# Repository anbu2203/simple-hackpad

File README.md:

#  Simple Hackpad

A custom 4-key macro pad designed for productivity and built with the Seeed Studio XIAO RP2040. This project uses KMK Firmware (CircuitPython) to handle custom keymaps and RGB lighting effects.

### PCB Layout

This layout features optimized trace widths for power delivery to the LEDs.

### Schematic

The circuit design utilizes a direct-pin connection, avoiding the complexity of a diode matrix for a small 4-key setup.

### 3D CAD View - Style 1

### 3D CAD View - Style 2

### 3D CAD View - Full Assembly

This view was critical for ensuring the USB-C port on the XIAO would be easily accessible through a case cutout.

### 3D PCB VIEW:

This is a 3D render generated within KiCad to preview the final manufactured board.

### 3D full hackpad 
 
 It helped me visualize the spacing between the mechanical switches and the board edge.
 This is the master assembly model combining the PCB, switches, and the switch plate.

## Firmware & Features
The firmware is built using KMK. It includes:
- Custom Macros: Configured for KiCad shortcuts and media controls.
- RGB Screensaver:A rainbow animation that activates during idle time.
- CircuitPython: Easy to edit on the fly by just saving the `code.py` file.

## Repository Structure
- `firmware`: The `code.py` and configuration files for KMK.
- `hardware`: KiCad schematic and the `.step` 3D model.
- `README-IMAGES`: Visuals used in this documentation.

### Specifications BOM:

- 4x Cherry MX Switches
- 2x SK6812 MINI Leds
- 1x XIAO RP2040
- 4x Blank DSA Keycaps
- 4x M3x16 Bolt
- 4x M3 Heatset

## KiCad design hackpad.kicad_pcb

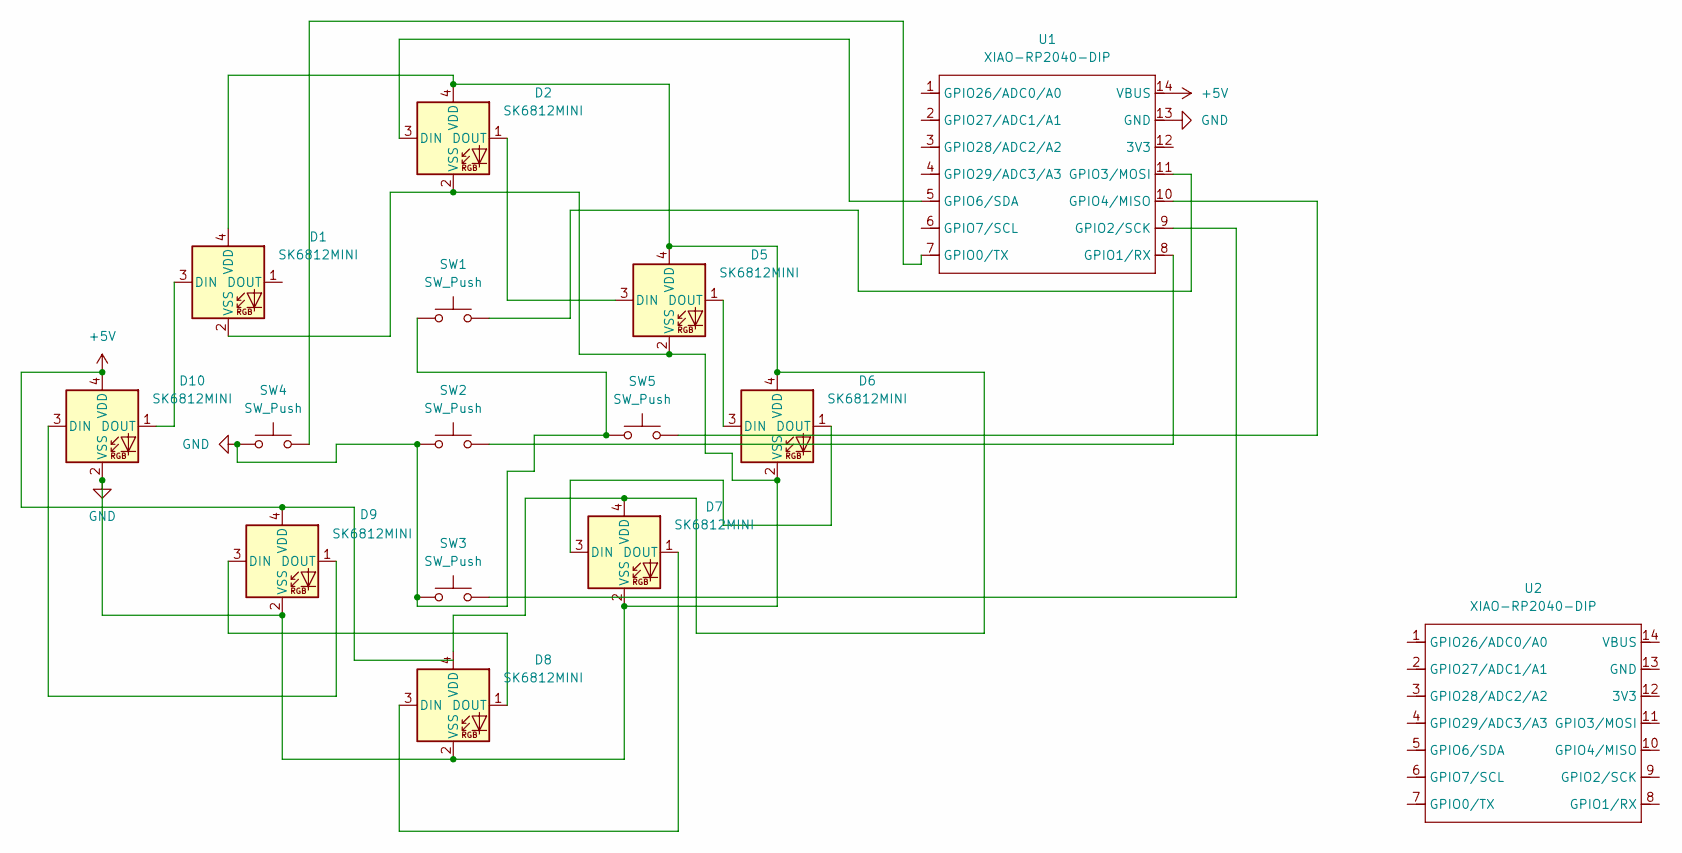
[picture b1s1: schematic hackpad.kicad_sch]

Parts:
D1, D2, D5, D6, D7, D8, D9, D10: SK6812MINI; LED_SK6812MINI_PLCC4_3.5x3.5mm_P1.75mm
SW1, SW2, SW3, SW4, SW5: SW_Push; SW_Cherry_MX_1.00u_PCB
U1, U2: XIAO-RP2040-DIP; MCU_Seeed_ESP32C3

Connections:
+5V: D9.4 (VDD), D10.4 (VDD), U1.14 (VBUS)
GND: D1.2 (VSS), D2.2 (VSS), D5.2 (VSS), D6.2 (VSS), D7.2 (VSS), D8.2 (VSS), D9.2 (VSS), D10.2 (VSS), SW1.1, SW2.1, SW3.1, SW4.1, SW5.1, U1.13 (GND)
unnamed: D1.3 (DIN), D10.1 (DOUT)
unnamed: D1.4 (VDD), D2.4 (VDD), D5.4 (VDD), D6.4 (VDD), D7.4 (VDD), D8.4 (VDD)
unnamed: D2.3 (DIN), U1.5 (GPIO6/SDA)
unnamed: D2.1 (DOUT), D5.3 (DIN)
unnamed: D5.1 (DOUT), D6.3 (DIN)
unnamed: D6.1 (DOUT), D7.3 (DIN)
unnamed: D7.1 (DOUT), D8.3 (DIN)
unnamed: D8.1 (DOUT), D9.3 (DIN)
unnamed: D9.1 (DOUT), D10.3 (DIN)
unnamed: SW4.2, U1.7 (GPIO0/TX)
unnamed: SW2.2, U1.8 (GPIO1/RX)
unnamed: SW3.2, U1.9 (GPIO2/SCK)
unnamed: SW1.2, U1.11 (GPIO3/MOSI)
unnamed: SW5.2, U1.10 (GPIO4/MISO)

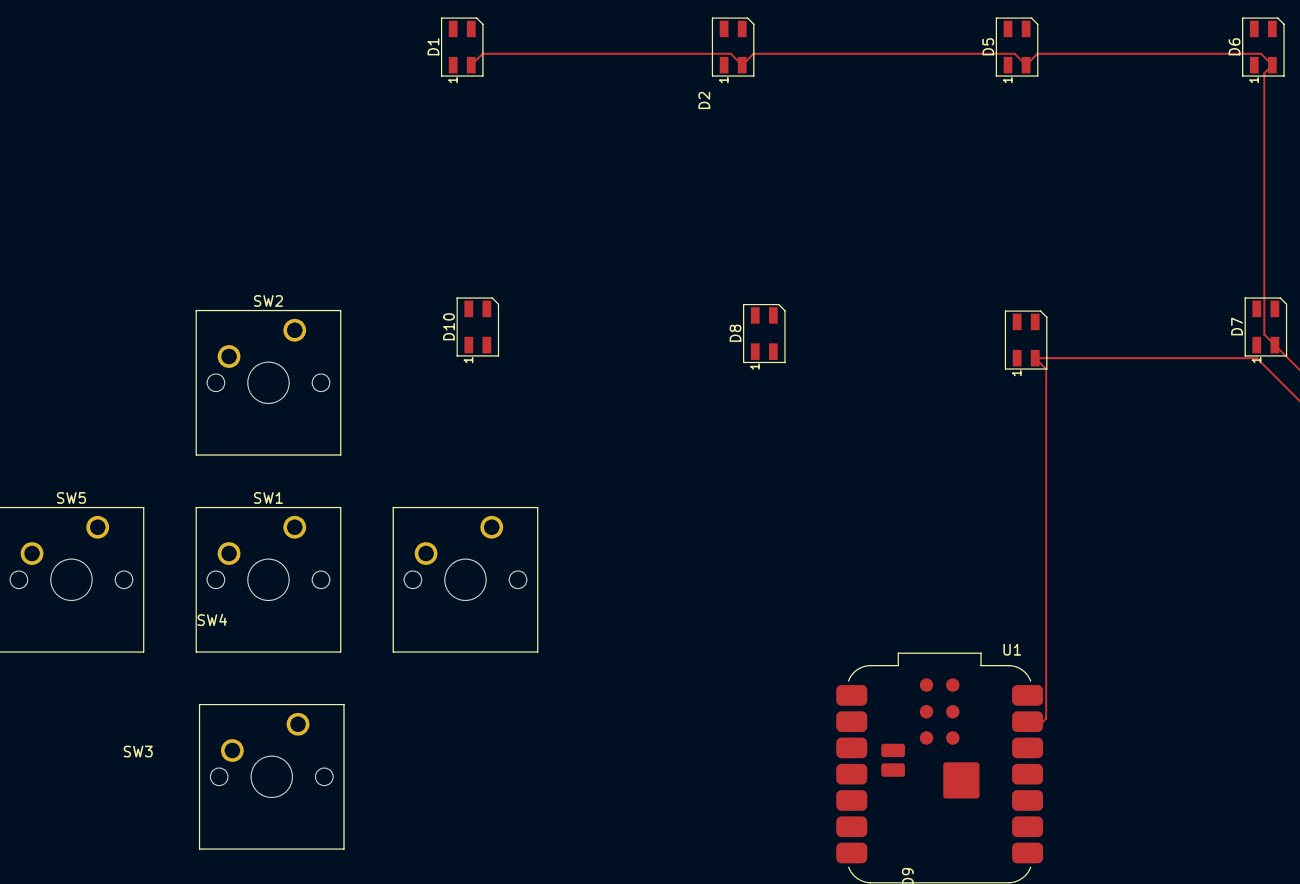
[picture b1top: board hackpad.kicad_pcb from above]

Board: 2 copper layers, 14 parts (0 on the bottom side), 16 nets.

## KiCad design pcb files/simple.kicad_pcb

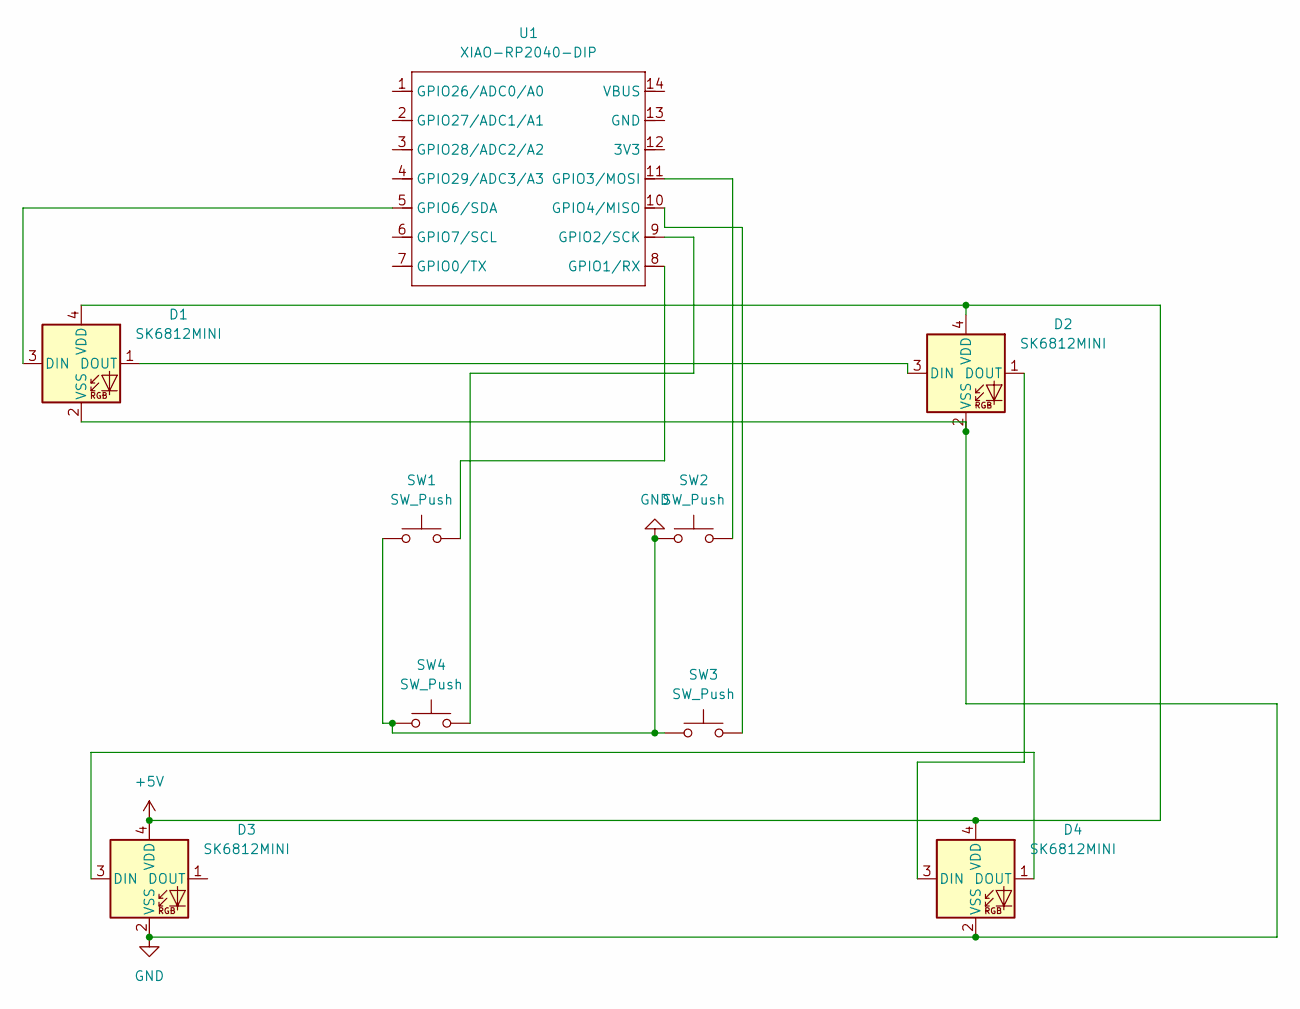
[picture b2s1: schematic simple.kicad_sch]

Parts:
D1, D2, D3, D4: SK6812MINI; LED_SK6812MINI_PLCC4_3.5x3.5mm_P1.75mm
SW1, SW2, SW3, SW4: SW_Push; SW_Cherry_MX_1.00u_PCB
U1: XIAO-RP2040-DIP; MOUDLE14P-XIAO-DIP-SMD

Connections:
+5V: D1.4 (VDD), D2.4 (VDD), D3.4 (VDD), D4.4 (VDD), U1.14 (VBUS)
GND: D1.2 (VSS), D2.2 (VSS), D3.2 (VSS), D4.2 (VSS), SW1.1, SW2.1, SW3.1, SW4.1, U1.13 (GND)
unnamed: D1.3 (DIN), U1.5 (GPIO6/SDA)
unnamed: D1.1 (DOUT), D2.3 (DIN)
unnamed: D2.1 (DOUT), D4.3 (DIN)
unnamed: D3.3 (DIN), D4.1 (DOUT)
unnamed: SW1.2, U1.8 (GPIO1/RX)
unnamed: SW4.2, U1.9 (GPIO2/SCK)
unnamed: SW2.2, U1.11 (GPIO3/MOSI)
unnamed: SW3.2, U1.10 (GPIO4/MISO)

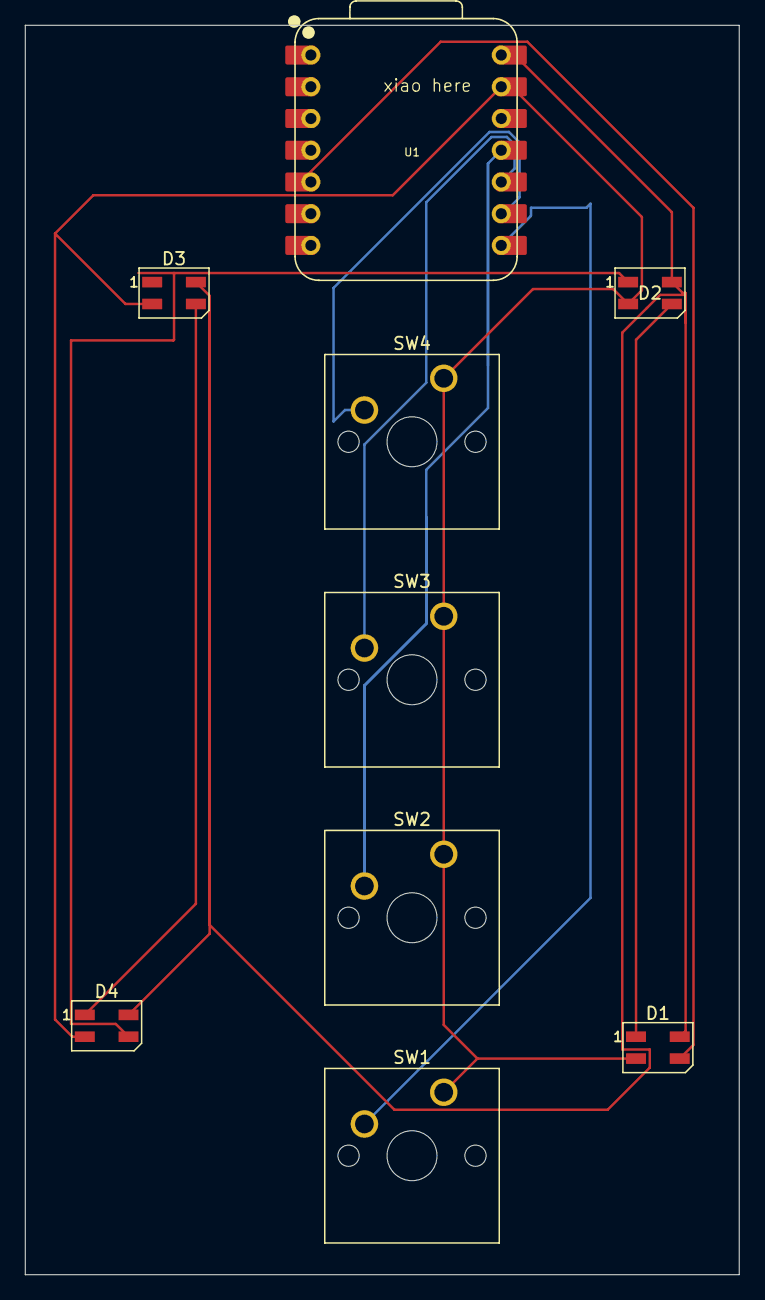
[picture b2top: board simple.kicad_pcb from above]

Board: 2 copper layers, 57.2 x 100.0 mm, 9 parts (0 on the bottom side), 10 nets.

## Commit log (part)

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2025-12-22 Enhance README with features and installation guide
    Expanded README with detailed features, hardware, installation instructions, and schematic information for the 4-key macro pad.
2025-12-23 Complete Hackpad project with KMK firmware
2025-12-23 Revise README for clarity and detail
    Updated README to enhance project description, features, and specifications.
2025-12-24 Add PCB layout image to README
2025-12-24 Fix typo in 3D PCB View section header
2026-06-30 Refactor firmware/code.py for clarity and structure
